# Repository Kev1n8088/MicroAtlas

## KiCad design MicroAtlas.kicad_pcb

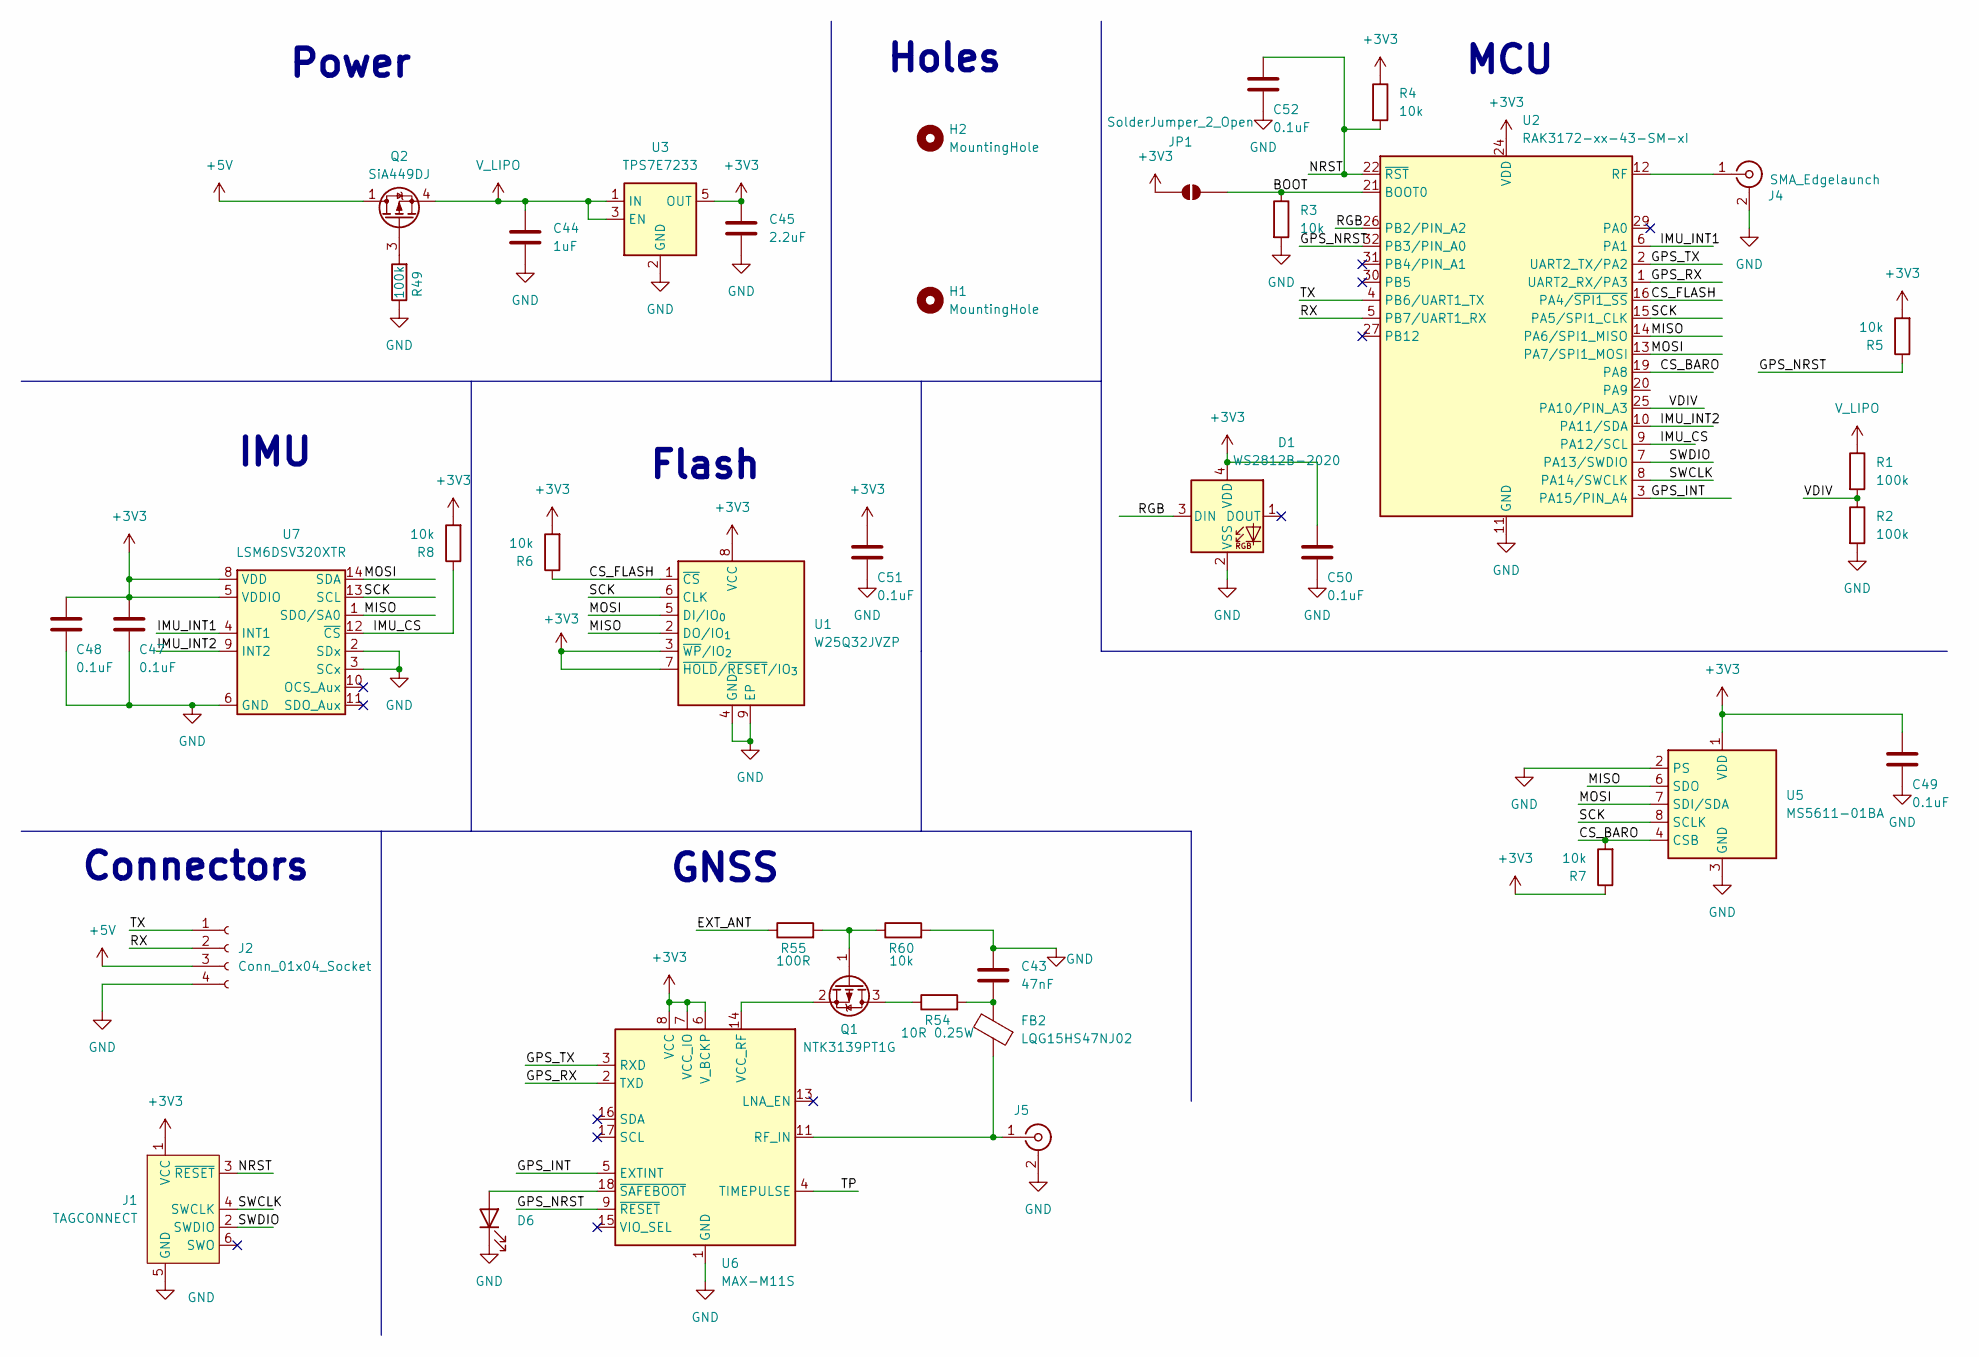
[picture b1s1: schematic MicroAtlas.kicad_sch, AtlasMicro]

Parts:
C43: 47nF; C_0402_1005Metric
C44: 1uF; C_0402_1005Metric
C45: 2.2uF; C_0402_1005Metric
C47, C48, C49, C50, C51, C52: 0.1uF; C_0402_1005Metric
D1: WS2812B-2020; LED_WS2812B-2020_PLCC4_2.0x2.0mm
D6: PPS; LED_0402_1005Metric
FB2: LQG15HS47NJ02; L_0402_1005Metric
H1: MountingHole; MountingHole_2.7mm_M2.5_DIN965_Pad
H2: MountingHole; MountingHole_2.7mm_Pad
J1: TAGCONNECT; Tag-Connect_TC2030-IDC-NL_2x03_P1.27mm_Vertical
J2: Conn_01x04_Socket; CONN_2200980000-SD_04P_MOL
J4: SMA_Edgelaunch; SMA_Amphenol_132289_EdgeMount
J5: UFL; U.FL_Molex_MCRF_73412-0110_Vertical
JP1: SolderJumper_2_Open; SolderJumper-2_P1.3mm_Open_RoundedPad1.0x1.5mm
Q1: NTK3139PT1G; SOT-723
Q2: SiA449DJ; Vishay_PowerPAK_SC70-6L_Single
R1, R2, R49: 100k; R_0402_1005Metric
R3, R4, R5, R6, R7, R8, R60: 10k; R_0402_1005Metric
R54: 10R 0.25W; R_0402_1005Metric
R55: 100R; R_0402_1005Metric
U1: W25Q32JVZP; WSON-8-1EP_6x5mm_P1.27mm_EP3.4x4.3mm
U2: RAK3172-xx-43-SM-xI; RAK3172
U3: TPS7E7233; SOT-23-5
U5: MS5611-01BA; LGA-8_3x5mm_P1.25mm
U6: MAX-M11S; ublox_MAX
U7: LSM6DSV320XTR; ST_LGA-14L_2.5x3.0mm_P0.5mm_4x3

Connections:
+3V3: C45.2, C47.2, C48.2, C49.2, C50.2, C51.2, D1.4 (VDD), J1.1 (VCC), JP1.1 (A), R4.1, R5.2, R6.2, R7.1, R8.2, U1.3 (~WP/IO_{2}), U1.7 (~HOLD/~RESET/IO_{3}), U1.8 (VCC), U2.24 (VDD), U3.5 (OUT), U5.1 (VDD), U6.6 (V_BCKP), U6.7 (VCC_IO), U6.8 (VCC), U7.5 (VDDIO), U7.8 (VDD)
+5V: J2.3, Q2.1 (D)
/BOOT: JP1.2 (B), R3.1, U2.21 (BOOT0)
/CS_BARO: R7.2, U2.19 (PA8), U5.4 (CSB), U5.5 (CSB)
/CS_FLASH: R6.1, U1.1 (~CS), U2.16 (PA4/~SPI1_SS)
/EXT_ANT: R55.1
/GPS_INT: U2.3 (PA15/PIN_A4), U6.5 (EXTINT)
/GPS_NRST: R5.1, U2.32 (PB3/PIN_A0), U6.9 (~RESET)
/GPS_RX: U2.1 (UART2_RX/PA3), U6.2 (TXD)
/GPS_TX: U2.2 (UART2_TX/PA2), U6.3 (RXD)
/IMU_CS: R8.1, U2.9 (PA12/SCL), U7.12 (~CS)
/IMU_INT1: U2.6 (PA1), U7.4 (INT1)
/IMU_INT2: U2.10 (PA11/SDA), U7.9 (INT2)
/MISO: U1.2 (DO/IO_{1}), U2.14 (PA6/SPI1_MISO), U5.6 (SDO), U7.1 (SDO/SA0)
/MOSI: U1.5 (DI/IO_{0}), U2.13 (PA7/SPI1_MOSI), U5.7 (SDI/SDA), U7.14 (SDA)
/NRST: C52.2, J1.3 (~RESET), R4.2, U2.22 (~RST)
/RGB: D1.3 (DIN), U2.26 (PB2/PIN_A2)
/RX: J2.2, U2.5 (PB7/UART1_RX)
/SCK: U1.6 (CLK), U2.15 (PA5/SPI1_CLK), U5.8 (SCLK), U7.13 (SCL)
/SWCLK: J1.4 (SWCLK), U2.8 (PA14/SWCLK)
/SWDIO: J1.2 (SWDIO), U2.7 (PA13/SWDIO)
/TP: U6.4 (TIMEPULSE)
/TX: J2.1, U2.4 (PB6/UART1_TX)
/VDIV: R1.2, R2.1, U2.25 (PA10/PIN_A3)
GND: C43.2, C44.1, C45.1, C47.1, C48.1, C49.1, C50.1, C51.1, C52.1, D1.2 (VSS), D6.1 (K), J1.5 (GND), J2.4, J4.2 (Ext), J5.2 (Ext), R2.2, R3.2, R49.1, R60.2, U1.4 (GND), U1.9 (EP), U2.11 (GND), U2.17 (GND), U2.18 (GND), U2.23 (GND), U2.28 (GND), U3.2 (GND), U5.2 (PS), U5.3 (GND), U6.1 (GND), U6.10 (GND), U6.12 (GND), U7.2 (SDx), U7.3 (SCx), U7.6 (GND), U7.7 (GND)
unnamed: C43.1, FB2.2, R54.2
unnamed: D6.2 (A), U6.18 (~SAFEBOOT)
unnamed: J4.1 (In), U2.12 (RF)
unnamed: FB2.1, J5.1 (In), U6.11 (RF_IN)
unnamed: Q1.3 (D), R54.1
unnamed: Q1.1 (G), R55.2, R60.1
unnamed: Q1.2 (S), U6.14 (VCC_RF)
unnamed: Q2.3 (G), R49.2
V_LIPO: C44.2, Q2.4 (S), R1.1, U3.1 (IN), U3.3 (EN)

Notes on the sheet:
GNSS
Connectors
IMU
Flash
MCU
Power
Holes

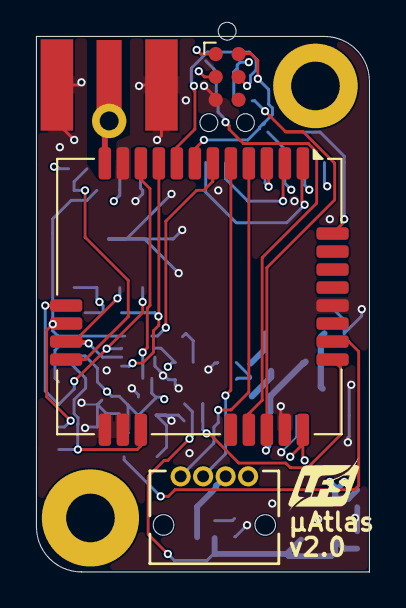
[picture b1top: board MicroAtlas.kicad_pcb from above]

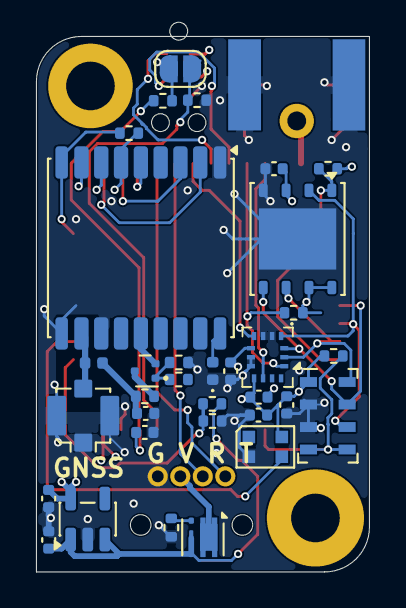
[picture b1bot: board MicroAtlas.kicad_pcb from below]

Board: 4 copper layers, 18.5 x 29.8 mm, 39 parts (33 on the bottom side), 32 nets.
